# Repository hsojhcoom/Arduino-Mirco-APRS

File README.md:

# Arduino-Mirco-APRS

This is a design based on the Mircomodem and LibAPRS (links below).I used the design to create my own boards for a cheaper mobile solution. The different boards are designed around the ATMega 328P uC chip, other chips arduino uses will not work without heavy mods to the libraries.

I will contiune to update the PCB files, with new board designs for different radios.

Mircomodem-https://github.com/markqvist/MicroModem
LibAPRS- https://github.com/markqvist/LibAPRS

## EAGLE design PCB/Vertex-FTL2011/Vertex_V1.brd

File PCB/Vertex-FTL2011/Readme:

This board is designed for the the Vertex-FTL 2011. It is a great radio for APRS, they are cheap and durable.
It uses an RJ45 for the mic, and the board is designed with an RJ45 for direct connections
Along with the TX, the board can hand RX as well, two pads are there to connected a 3.5 jack (female). 

The uC is an Arduino Pro Mini either 5v or 3v3 versions. Along with the uC the board includes a Ublox Neo 6m GPS module.

[url=https://flic.kr/p/NSn6vw][img]https://c5.staticflickr.com/6/5803/30762352012_96a7987ef3.jpg[/img][/url][url=https://flic.kr/p/NSn6vw]f59d448a-a605-11e6-9024-55bf624ab5a8[/url] by [url=https://www.flickr.com/photos/77812812@N02/]Pickles_21[/url], on Flickr

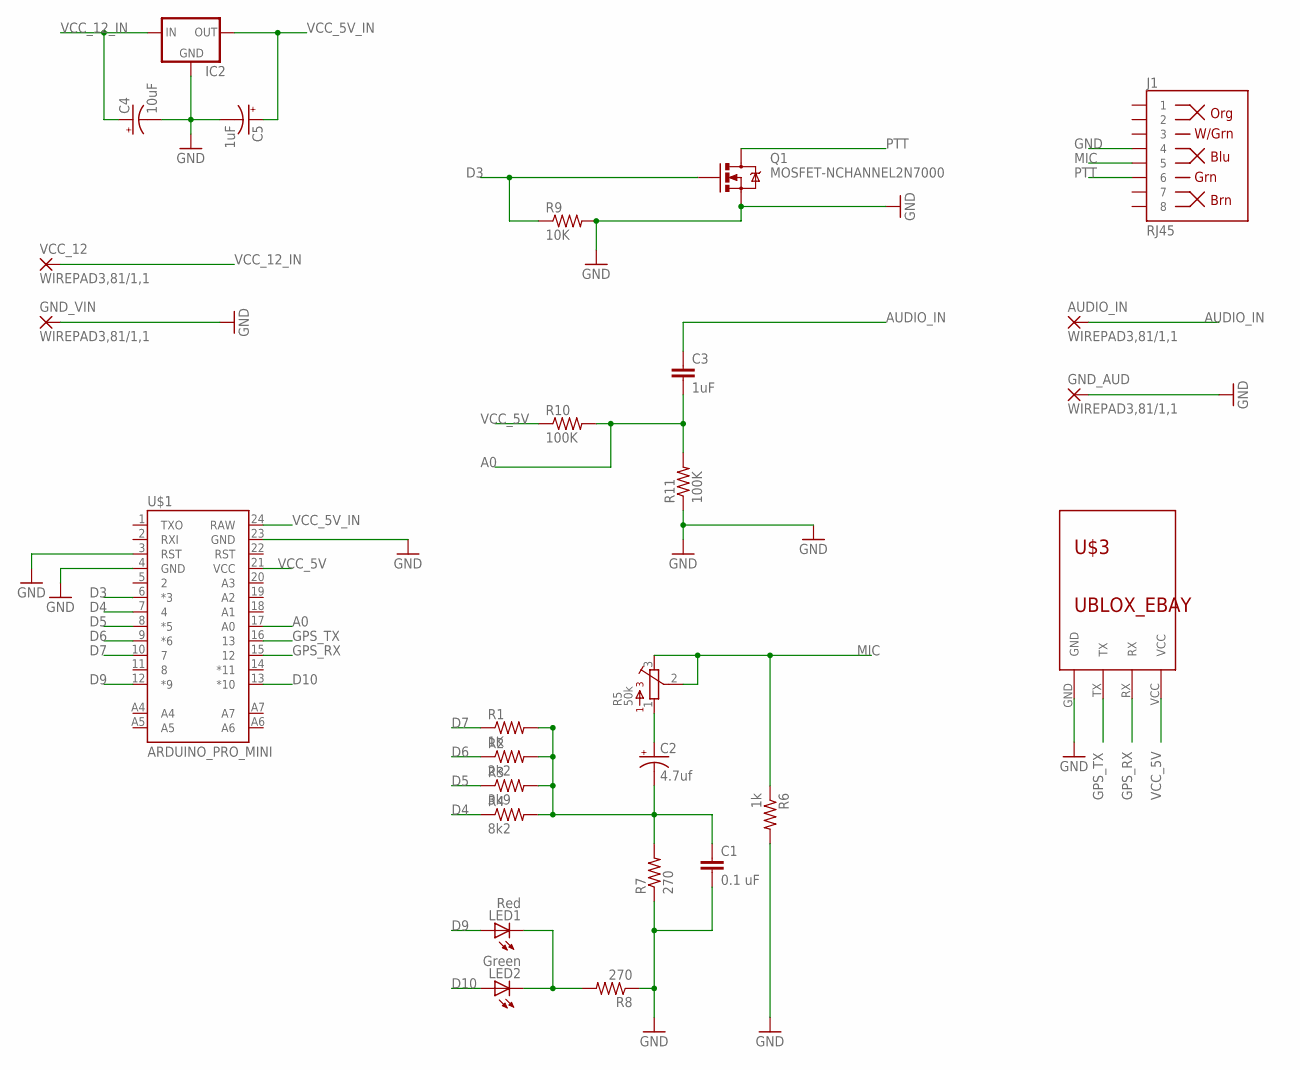
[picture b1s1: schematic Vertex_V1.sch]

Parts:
AUDIO_IN: WIREPAD3,81/1,1; 3,81/1,1
C1: 0.1 uF; CAP-PTH-SMALL-KIT
C2: 4.7uf; CPOL-RADIAL-10UF-25V
C3: 1uF; CAP-PTH-SMALL-KIT
C4: 10uF; CPOL-RADIAL-10UF-25V
C5: 1uF; CPOL-RADIAL-10UF-25V
GND_AUD: WIREPAD3,81/1,1; 3,81/1,1
GND_VIN: WIREPAD3,81/1,1; 3,81/1,1
IC2: 78XXS
J1: RJ45; RJ45-8
LED1: Red; LED5MM
LED2: Green; LED5MM
Q1: MOSFET-NCHANNEL2N7000; TO-92
R1: 1K; 0309V
R2: 2k2; 0309V
R3: 3k9; 0309V
R4: 8k2; 0309V
R5: 50k; 3362P
R6: 1k; 0309V
R7, R8: 270; 0309V
R9: 10K; 0309V
R10, R11: 100K; 0309V
U$1: ARDUINO_PRO_MINI
U$3: UBLOX_EBAY
VCC_12: WIREPAD3,81/1,1; 3,81/1,1

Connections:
A0: C3.2, R10.2, R11.2, U$1.17 (A0)
AUDIO_IN: AUDIO_IN.1, C3.1
D3: Q1.2 (G), R9.1, U$1.6 (*3)
D4: R4.1, U$1.7 (4)
D5: R3.1, U$1.8 (*5)
D6: R2.1, U$1.9 (*6)
D7: R1.1, U$1.10 (7)
D9: LED1.A, U$1.12 (*9)
D10: LED2.A, U$1.13 (*10)
GND: C1.2, C4.2 (-), C5.2 (-), GND_AUD.1, GND_VIN.1, IC2.GND, J1.4, Q1.1 (S), R6.2, R7.1, R8.1, R9.2, R11.1, U$1.3 (RST), U$1.4 (GND), U$1.23 (GND), U$3.GND
GPS_RX: U$1.15 (12), U$3.RX
GPS_TX: U$1.16 (13), U$3.TX
MIC: J1.5, R5.2, R5.3, R6.1
unnamed: C1.1, C2.2 (-), R1.2, R2.2, R3.2, R4.2, R7.2
unnamed: C2.1 (+), R5.1
unnamed: LED1.K (C), LED2.K (C), R8.2
PTT: J1.6, Q1.3 (D)
VCC_5V: R10.1, U$1.21 (VCC), U$3.VCC
VCC_5V_IN: C5.1 (+), IC2.OUT, U$1.24 (RAW)
VCC_12_IN: C4.1 (+), IC2.IN, VCC_12.1

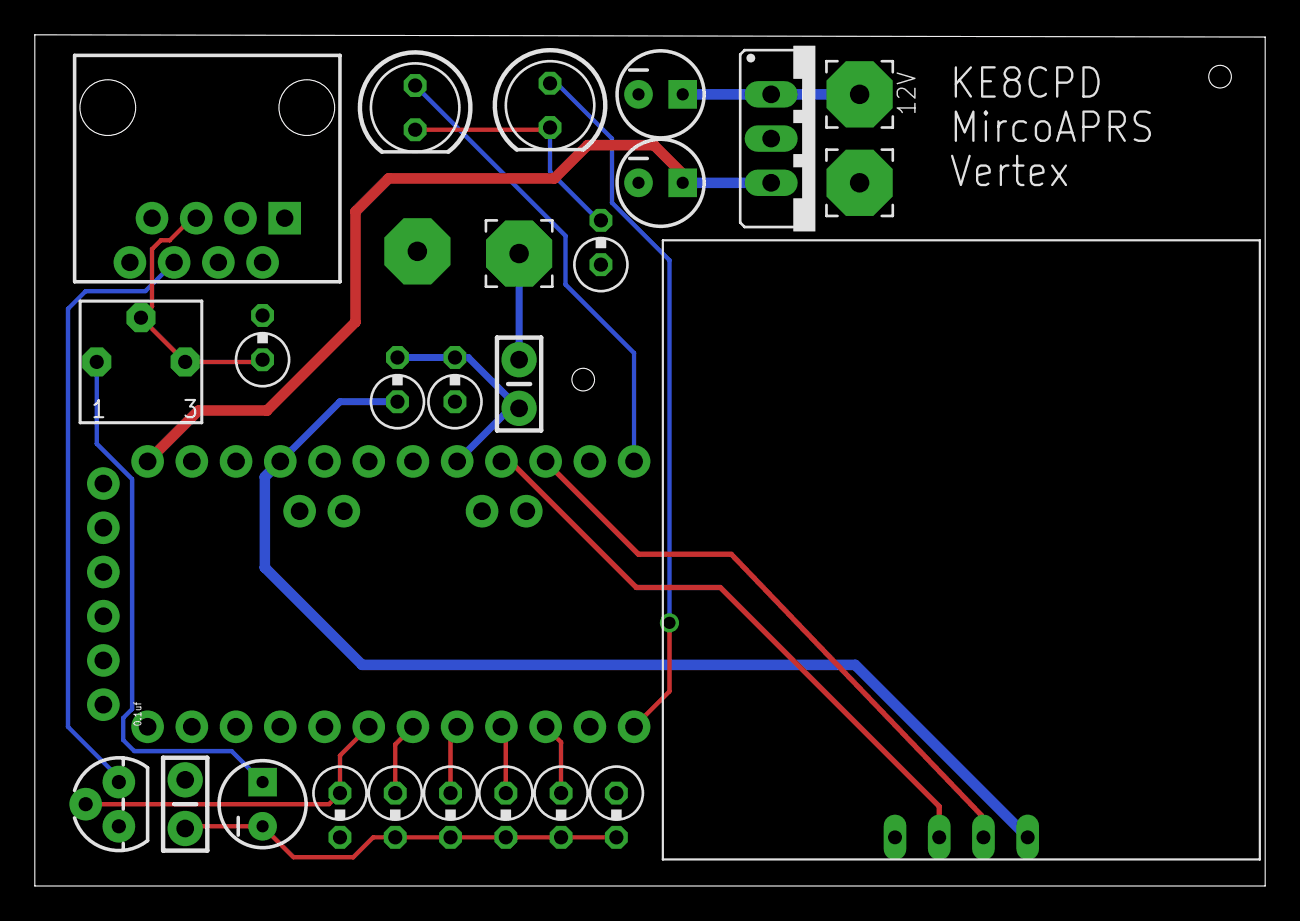
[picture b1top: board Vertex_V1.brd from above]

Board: 2 copper layers, 70.7 x 48.9 mm, 27 parts (1 on the bottom side), 20 nets.

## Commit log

2016-11-08 Created
2016-11-08 Quick Notes on Design
2016-11-09 Added Photo

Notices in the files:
parts and their libraries:
SparkFun-Capacitors: Licensing: Creative Commons ShareAlike 4.0 International - https://creativecommons.org/licenses/by-sa/4.0
